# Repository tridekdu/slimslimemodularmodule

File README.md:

# Slim and modular SlimeVR module
## Goals
* Easy wiring and provide supplementary components (caps, etc.)
* Support many readymade AliExpress-tier modules (they seem to have similar pinouts)
* Be compatible with SlimeVR
* Provide wide selection of power input methods

## Needed parts
### PCB
* SW1 = PCM12 slide switch
* R1, R2, R3 = 10K pull-up/down resistors for ESP
* R4 and R5 = Similar sized resistor ~100K (battery monitor voltage divider)
* 100n bypass caps
* Optional AMS1117-3.3V regulator
* Optional 1N5817 Diode

SMD components are 0805 sized

### External modules
* Accelerometer module (for example: MPU6XXX or BNO08X)
* Power management module (for example: TP4056)
* Lithium battery

## Design sketches

## Example

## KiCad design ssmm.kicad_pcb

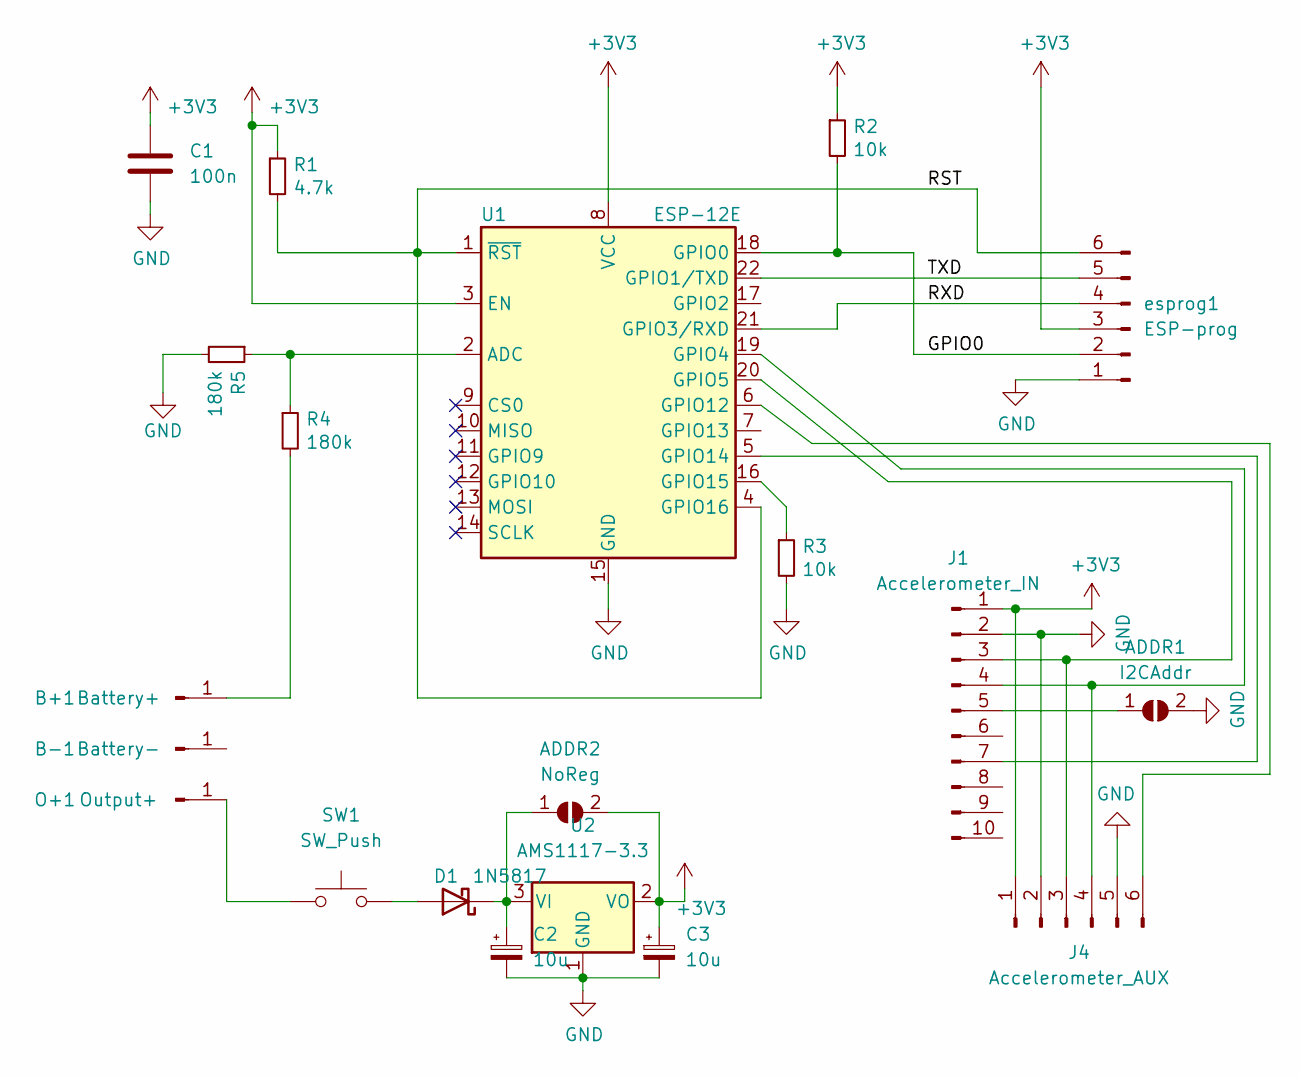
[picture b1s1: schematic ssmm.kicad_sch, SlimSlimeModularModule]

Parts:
ADDR1: I2CAddr; SolderJumper-2_P1.3mm_Open_RoundedPad1.0x1.5mm
ADDR2: NoReg; SolderJumper-2_P1.3mm_Open_RoundedPad1.0x1.5mm
B+1: Battery+; PinHeader_1x01_P2.54mm_Vertical
B-1: Battery-; PinHeader_1x01_P2.54mm_Vertical
C1: 100n; C_1210_3225Metric
C2, C3: 10u; CP_EIA-6032-20_AVX-F_Pad2.25x2.35mm_HandSolder
D1: 1N5817; D_MiniMELF_Handsoldering
J1: Accelerometer_IN; PinHeader_1x10_P2.54mm_Vertical
J4: Accelerometer_AUX; Molex_Micro-Fit_3.0_43045-0600_2x03_P3.00mm_Horizontal
O+1: Output+; PinHeader_1x01_P2.54mm_Vertical
R1: 4.7k; R_0805_2012Metric_Pad1.20x1.40mm_HandSolder
R2, R3: 10k; R_0805_2012Metric_Pad1.20x1.40mm_HandSolder
R4, R5: 180k; R_0805_2012Metric_Pad1.20x1.40mm_HandSolder
SW1: SW_Push; SW_SPDT_PCM12
U1: ESP-12E
U2: AMS1117-3.3; SOT-223-3_TabPin2
esprog1: ESP-prog; PinHeader_1x06_P2.54mm_Vertical

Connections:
+3V3: ADDR2.2 (B), C1.1, C3.1, J1.1, J4.1, R1.1, R2.1, U1.3 (EN), U1.8 (VCC), U2.2 (VO), esprog1.3
/GPIO0: R2.2, U1.18 (GPIO0), esprog1.2
/RST: R1.2, U1.1 (~RST), U1.4 (GPIO16), esprog1.6
/RXD: U1.21 (GPIO3/RXD), esprog1.4
/TXD: U1.22 (GPIO1/TXD), esprog1.5
GND: ADDR1.2 (B), C1.2, C2.2, C3.2, J1.2, J4.2, J4.5, R3.2, R5.2, U1.15 (GND), U2.1 (GND), esprog1.1
unnamed: ADDR1.1 (A), J1.5
unnamed: ADDR2.1 (A), C2.1, D1.1 (K), U2.3 (VI)
unnamed: B+1.1, R4.2
unnamed: D1.2 (A), SW1.2
unnamed: J1.3, J4.3, U1.20 (GPIO5)
unnamed: J1.4, J4.4, U1.19 (GPIO4)
unnamed: J1.7, U1.5 (GPIO14)
unnamed: J1.8, U1.7 (GPIO13)
unnamed: J4.6, U1.6 (GPIO12)
unnamed: O+1.1, SW1.1
unnamed: R3.1, U1.16 (GPIO15)
unnamed: R4.1, R5.1, U1.2 (ADC)

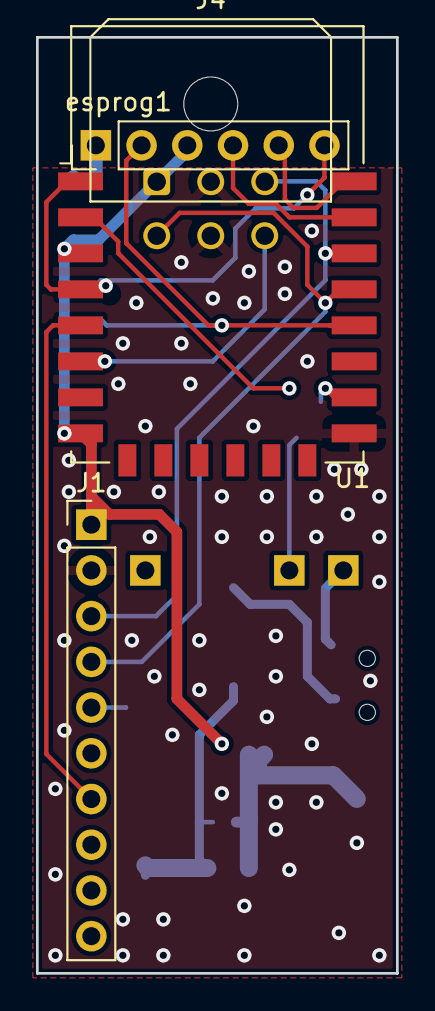
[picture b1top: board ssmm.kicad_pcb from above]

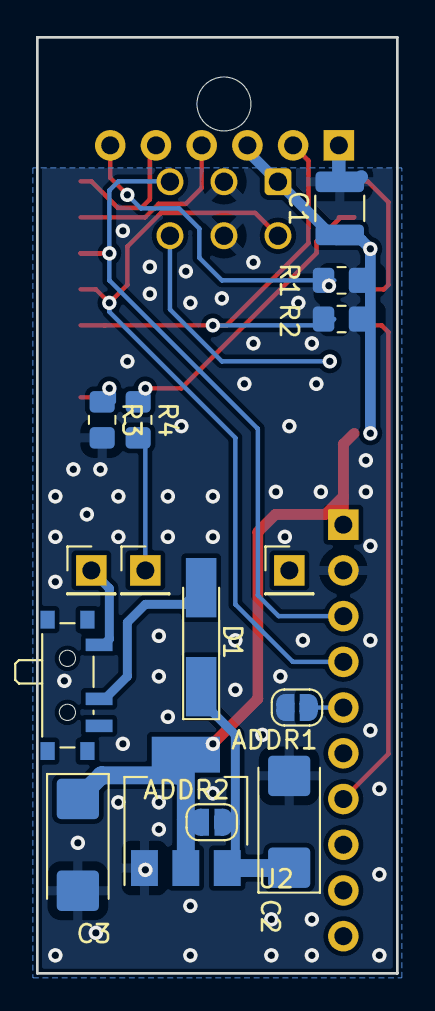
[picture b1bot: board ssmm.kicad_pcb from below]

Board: 2 copper layers, 20.0 x 52.0 mm, 19 parts (15 on the bottom side), 18 nets.

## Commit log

2024-08-21 Boards :3
2024-08-21 Example images
2024-08-25 Usability++
